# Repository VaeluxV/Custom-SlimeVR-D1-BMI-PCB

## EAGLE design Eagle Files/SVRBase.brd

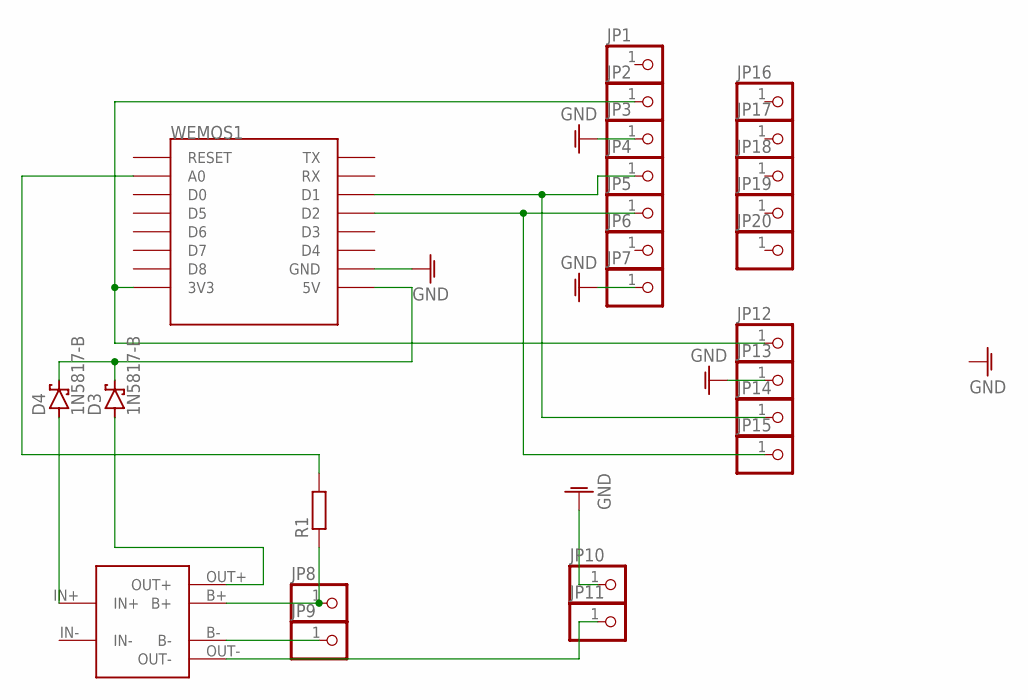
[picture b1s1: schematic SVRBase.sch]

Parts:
CHARGING: TP4056-PTH
D3, D4: 1N5817-B; DO41-7.6
JP1, JP2, JP3, JP4, JP5, JP6, JP7, JP8, JP9, JP10, JP11, JP12, JP13, JP14, JP15, JP16, JP17, JP18, JP19, JP20: PINHD-1X1; 1X01
R1: R-EU_0204/7; 0204/7
WEMOS1: WEMOS-D1-MINI

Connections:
GNDA: JP3.1, JP7.1, JP10.1, JP13.1, WEMOS1.GND
unnamed: JP4.1, JP14.1, WEMOS1.D1
unnamed: JP2.1, JP12.1, WEMOS1.3V3
unnamed: CHARGING.B+, JP8.1, R1.1
unnamed: D3.C, D4.C, WEMOS1.5V
unnamed: CHARGING.IN+, D4.A
unnamed: CHARGING.OUT+, D3.A
unnamed: CHARGING.B-, JP9.1
unnamed: R1.2, WEMOS1.A0
unnamed: CHARGING.OUT-, JP11.1
unnamed: JP5.1, JP15.1, WEMOS1.D2

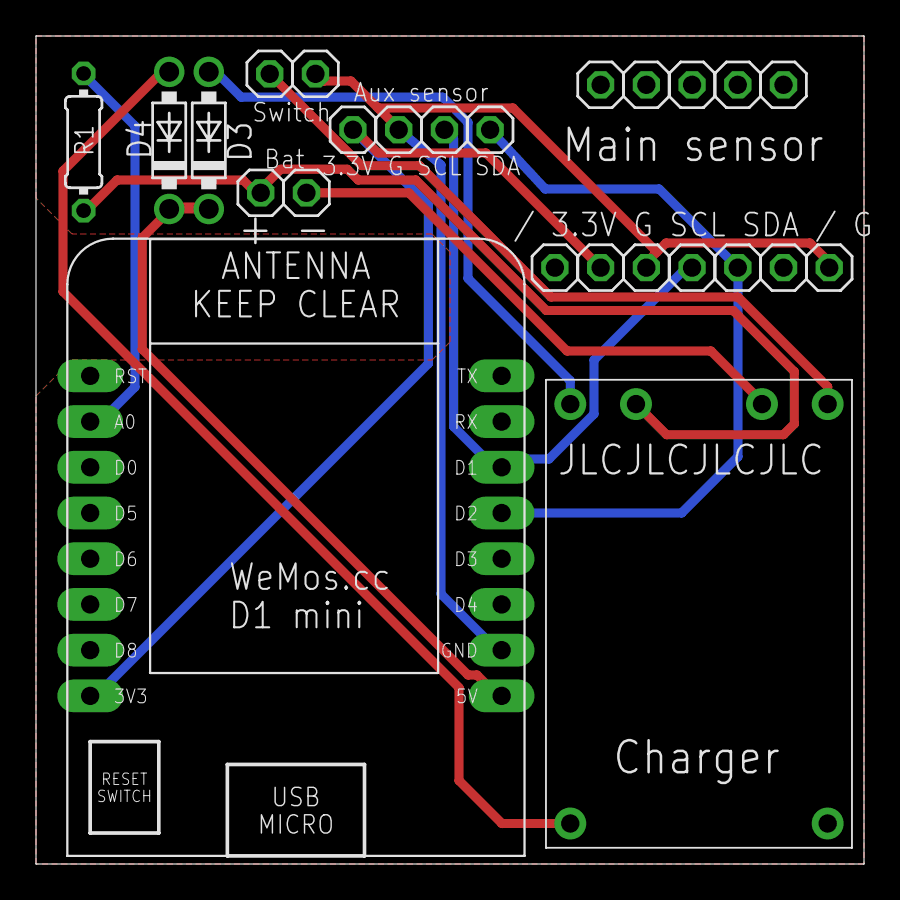
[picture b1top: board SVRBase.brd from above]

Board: 2 copper layers, 46.0 x 46.0 mm, 25 parts (0 on the bottom side), 11 nets.

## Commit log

2024-05-28 Update LICENSE
2024-05-28 Add files for V1.3.2
